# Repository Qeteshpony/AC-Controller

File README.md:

# Qeteshs AC-Controller

[Hardware Documentation](https://qeteshpony.github.io/AC-Controller)

Simple controller for IoT devices with ESP-Home and Home Assistant in mind. This project was mainly started to get better control for our AC system but I guess it can be adapted for about anything. 

The system is based on an ESP32 module, a small LCD and two rotary encoders with optional support for charging and using a LiPo battery. 

The hardware was designed for production by JLCPCB and as many parts as possible were selected from their basic parts library to keep costs low. 

The PCB has two positions for a USB-C port, both are wired in parallel so only one should be soldered in - which one depends on the usecase. 

The display I use is the `DEM 16226 SYH-LY` which is smaller than most 16x2 character displays and available from several retailers. The board most likely needs major changes to be used with another display since the connector is in a different position to most.

I also got shorter 2.54mm headers that only raise the display by about 8mm from the main board so everything is more compact.

The battery used is a 2500 mAH LiPo cell called `LP-785060` with built in protection circuit and about the same measurements as the board so it fits neatly underneath it.

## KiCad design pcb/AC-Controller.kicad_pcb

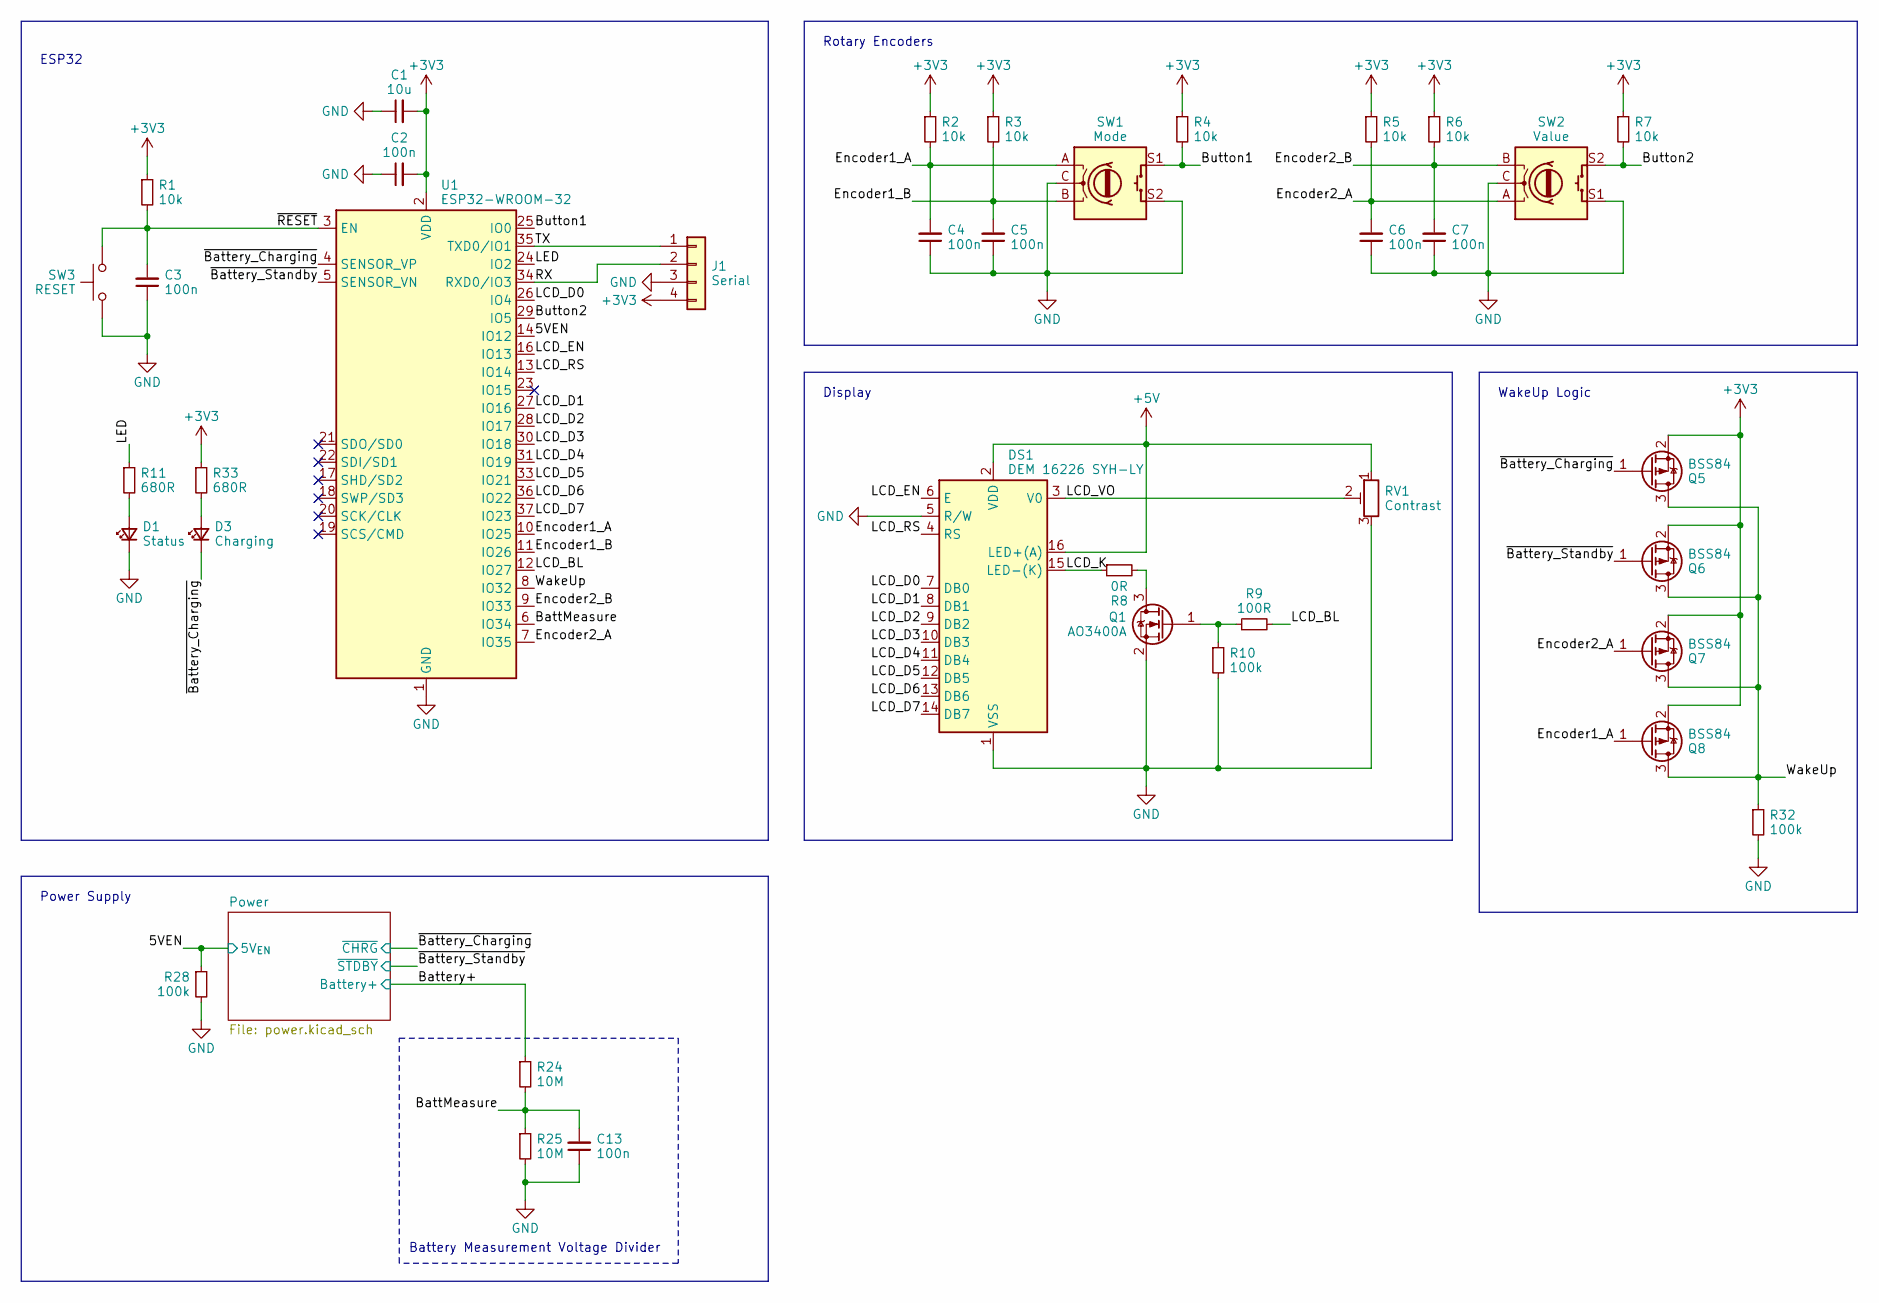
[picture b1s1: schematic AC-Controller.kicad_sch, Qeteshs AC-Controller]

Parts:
C1: 10u; C_0402_1005Metric; LCSC C15525
C2, C3, C4, C5, C6, C7, C13: 100n; C_0402_1005Metric; LCSC C1525
D1: Status; LED_0603_1608Metric; LCSC C2286
D3: Charging; LED_0603_1608Metric; LCSC C2286
DS1: DEM 16226 SYH-LY
J1: Serial; PinSocket_1x04_P2.54mm_Vertical
Q1: AO3400A; SOT-23; LCSC C20917
Q5, Q6, Q7, Q8: BSS84; SOT-23; LCSC C8492
R1, R2, R3, R4, R5, R6, R7: 10k; R_0402_1005Metric; LCSC C25744
R8: 0R; R_0603_1608Metric_Pad0.98x0.95mm_HandSolder; LCSC C21189
R9: 100R; R_0402_1005Metric; LCSC C25076
R10, R28, R32: 100k; R_0402_1005Metric; LCSC C25741
R11, R33: 680R; R_0402_1005Metric; LCSC C25130
R24, R25: 10M; R_0402_1005Metric; LCSC C26082
RV1: Contrast; Potentiometer_Runtron_RM-065_Vertical
SW1: Mode; RotaryEncoder_Alps_EC12E-Switch_Vertical_H20mm
SW2: Value; RotaryEncoder_Alps_EC12E-Switch_Vertical_H20mm
SW3: RESET; SW_Push_1P1T_XKB_TS-1187A; LCSC C318884
U1: ESP32-WROOM-32; LCSC C82899

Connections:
+3V3: C1.2, C2.2, J1.4, Q5.2 (S), Q6.2 (S), Q7.2 (S), Q8.2 (S), R1.1, R2.1, R3.1, R4.1, R5.1, R6.1, R7.1, R33.1, U1.2 (VDD); also elsewhere on the board
+5V: DS1.2 (VDD), DS1.16 (LED+(A)), RV1.1; also elsewhere on the board
/5VEN: R28.1, U1.14 (IO12); also elsewhere on the board
/BattMeasure: C13.2, R24.2, R25.1, U1.6 (IO34)
/Battery+: R24.1; also elsewhere on the board
/Button1: R4.2, SW1.S1, U1.25 (IO0)
/Button2: R7.2, SW2.S2, U1.29 (IO5)
/Encoder1_A: C4.2, Q8.1 (G), R2.2, SW1.A, U1.10 (IO25)
/Encoder1_B: C5.2, R3.2, SW1.B, U1.11 (IO26)
/Encoder2_A: C6.2, Q7.1 (G), R5.2, SW2.A, U1.7 (IO35)
/Encoder2_B: C7.2, R6.2, SW2.B, U1.9 (IO33)
/LCD_BL: R9.2, U1.12 (IO27)
/LCD_D0: DS1.7 (DB0), U1.26 (IO4)
/LCD_D1: DS1.8 (DB1), U1.27 (IO16)
/LCD_D2: DS1.9 (DB2), U1.28 (IO17)
/LCD_D3: DS1.10 (DB3), U1.30 (IO18)
/LCD_D4: DS1.11 (DB4), U1.31 (IO19)
/LCD_D5: DS1.12 (DB5), U1.33 (IO21)
/LCD_D6: DS1.13 (DB6), U1.36 (IO22)
/LCD_D7: DS1.14 (DB7), U1.37 (IO23)
/LCD_EN: DS1.6 (E), U1.16 (IO13)
/LCD_K: DS1.15 (LED-(K)), R8.1
/LCD_RS: DS1.4 (RS), U1.13 (IO14)
/LCD_VO: DS1.3 (V0), RV1.2
/LED: R11.1, U1.24 (IO2)
/RX: J1.2, U1.34 (RXD0/IO3)
/TX: J1.1, U1.35 (TXD0/IO1)
/WakeUp: Q5.3 (D), Q6.3 (D), Q7.3 (D), Q8.3 (D), R32.1, U1.8 (IO32)
/~Battery_Charging: D3.1 (K), Q5.1 (G), U1.4 (SENSOR_VP); also elsewhere on the board
/~Battery_Standby: Q6.1 (G), U1.5 (SENSOR_VN); also elsewhere on the board
/~RESET: C3.2, R1.2, SW3.2, U1.3 (EN)
GND: C1.1, C2.1, C3.1, C4.1, C5.1, C6.1, C7.1, C13.1, D1.1 (K), DS1.1 (VSS), DS1.5 (R/W), J1.3, Q1.2 (S), R10.2, R25.2, R28.2, R32.2, RV1.3, SW1.C, SW1.S2, SW2.C, SW2.S1, SW3.1, U1.1 (GND), U1.15 (GND), U1.38 (GND), U1.39 (GND); also elsewhere on the board
unnamed: D1.2 (A), R11.2
unnamed: D3.2 (A), R33.2
unnamed: Q1.3 (D), R8.2
unnamed: Q1.1 (G), R9.1, R10.1

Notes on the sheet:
Display
WakeUp Logic
ESP32
Battery Measurement Voltage Divider
Power Supply
Rotary Encoders

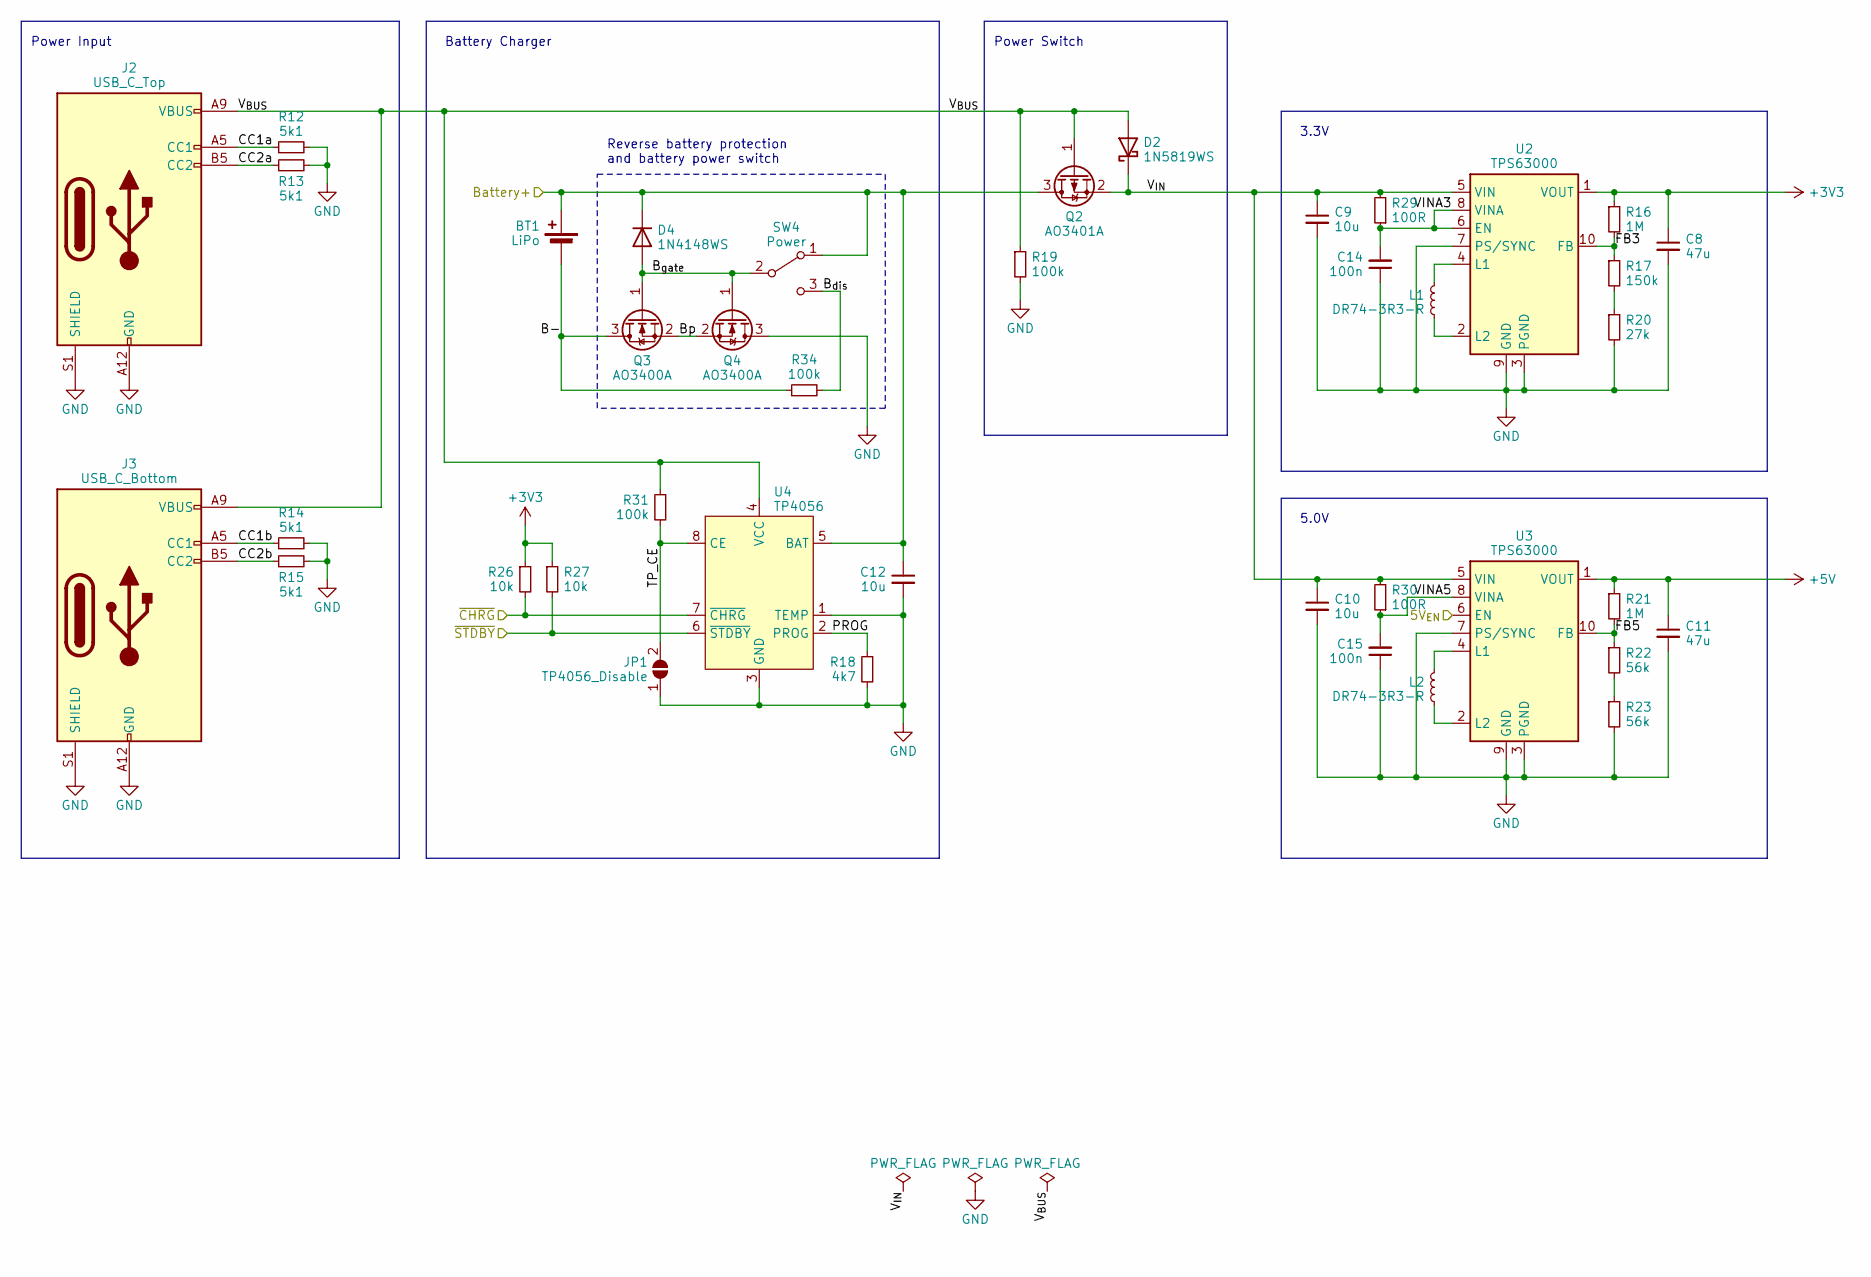
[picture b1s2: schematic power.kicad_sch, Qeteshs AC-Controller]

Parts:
BT1: LiPo; JST_PH_S2B-PH-K_1x02_P2.00mm_Horizontal
C8, C11: 47u; C_0805_2012Metric; LCSC C16780
C9, C10, C12: 10u; C_0603_1608Metric; LCSC C96446
C14, C15: 100n; C_0402_1005Metric; LCSC C1525
D2: 1N5819WS; D_SOD-323; LCSC C191023
D4: 1N4148WS; D_SOD-323; LCSC C2128
J2: USB_C_Top; GCT_USB4125-GF-A_REVA2; LCSC C283540
J3: USB_C_Bottom; GCT_USB4125-GF-A_REVA2; LCSC C283540
JP1: TP4056_Disable; SolderJumper-2_P1.3mm_Open_RoundedPad1.0x1.5mm
L1, L2: DR74-3R3-R; EATON_DR74
Q2: AO3401A; SOT-23; LCSC C15127
Q3, Q4: AO3400A; SOT-23; LCSC C20917
R12, R13, R14, R15: 5k1; R_0402_1005Metric; LCSC C25905
R16, R21: 1M; R_0402_1005Metric; LCSC C26083
R17: 150k; R_0402_1005Metric; LCSC C25755
R18: 4k7; R_0603_1608Metric_Pad0.98x0.95mm_HandSolder; LCSC C23162
R19, R31, R34: 100k; R_0402_1005Metric; LCSC C25741
R20: 27k; R_0402_1005Metric; LCSC C25771
R22, R23: 56k; R_0402_1005Metric; LCSC C25796
R26, R27: 10k; R_0402_1005Metric; LCSC C25744
R29, R30: 100R; R_0402_1005Metric; LCSC C25076
SW4: Power; SW_SPDT_PCM12; LCSC C221841
U2, U3: TPS63000; Texas_DRC0010J; LCSC C24966
U4: TP4056; SOP127P600X175-9N; LCSC C16581

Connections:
+3V3: C8.1, R16.1, R26.1, R27.1, U2.1 (VOUT); also elsewhere on the board
+5V: C11.1, R21.1, U3.1 (VOUT); also elsewhere on the board
/5VEN: U3.6 (EN); also elsewhere on the board
/Battery+: BT1.1 (+), C12.1, D4.1 (K), Q2.3 (D), SW4.1 (A), U4.5 (BAT); also elsewhere on the board
/Power/B-: BT1.2 (-), Q3.3 (D), R34.1
/Power/B_{dis}: R34.2, SW4.3 (C)
/Power/B_{gate}: D4.2 (A), Q3.1 (G), Q4.1 (G), SW4.2 (B)
/Power/Bp: Q3.2 (S), Q4.2 (S)
/Power/CC1a: J2.A5 (CC1), R12.1
/Power/CC1b: J3.A5 (CC1), R14.1
/Power/CC2a: J2.B5 (CC2), R13.1
/Power/CC2b: J3.B5 (CC2), R15.1
/Power/FB3: R16.2, R17.1, U2.10 (FB)
/Power/FB5: R21.2, R22.1, U3.10 (FB)
/Power/PROG: R18.1, U4.2 (PROG)
/Power/TP_CE: JP1.2 (B), R31.2, U4.8 (CE)
/Power/VINA3: C14.2, R29.1, U2.6 (EN), U2.8 (VINA)
/Power/VINA5: C15.2, R30.1, U3.8 (VINA)
/Power/V_{BUS}: D2.2 (A), J2.A9 (VBUS), J2.B9 (VBUS), J3.A9 (VBUS), J3.B9 (VBUS), Q2.1 (G), R19.1, R31.1, U4.4 (VCC)
/Power/V_{IN}: C9.1, C10.1, D2.1 (K), Q2.2 (S), R29.2, R30.2, U2.5 (VIN), U3.5 (VIN)
/~Battery_Charging: R26.2, U4.7 (~CHRG); also elsewhere on the board
/~Battery_Standby: R27.2, U4.6 (~STDBY); also elsewhere on the board
GND: C8.2, C9.2, C10.2, C11.2, C12.2, C14.1, C15.1, J2.A12 (GND), J2.B12 (GND), J2.S1 (SHIELD), J3.A12 (GND), J3.B12 (GND), J3.S1 (SHIELD), JP1.1 (A), Q4.3 (D), R12.2, R13.2, R14.2, R15.2, R18.2, R19.2, R20.2, R23.2, U2.3 (PGND), U2.7 (PS/SYNC), U2.9 (GND), U2.11 (PGND), U3.3 (PGND), U3.7 (PS/SYNC), U3.9 (GND), U3.11 (PGND), U4.1 (TEMP), U4.3 (GND), U4.9 (EP); also elsewhere on the board
unnamed: R17.2, R20.1
unnamed: R22.2, R23.1
unnamed: L1.2, U2.4 (L1)
unnamed: L1.1, U2.2 (L2)
unnamed: L2.2, U3.4 (L1)
unnamed: L2.1, U3.2 (L2)

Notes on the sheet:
Power Input
Power Switch
3.3V
Battery Charger
5.0V
Reverse battery protection and battery power switch

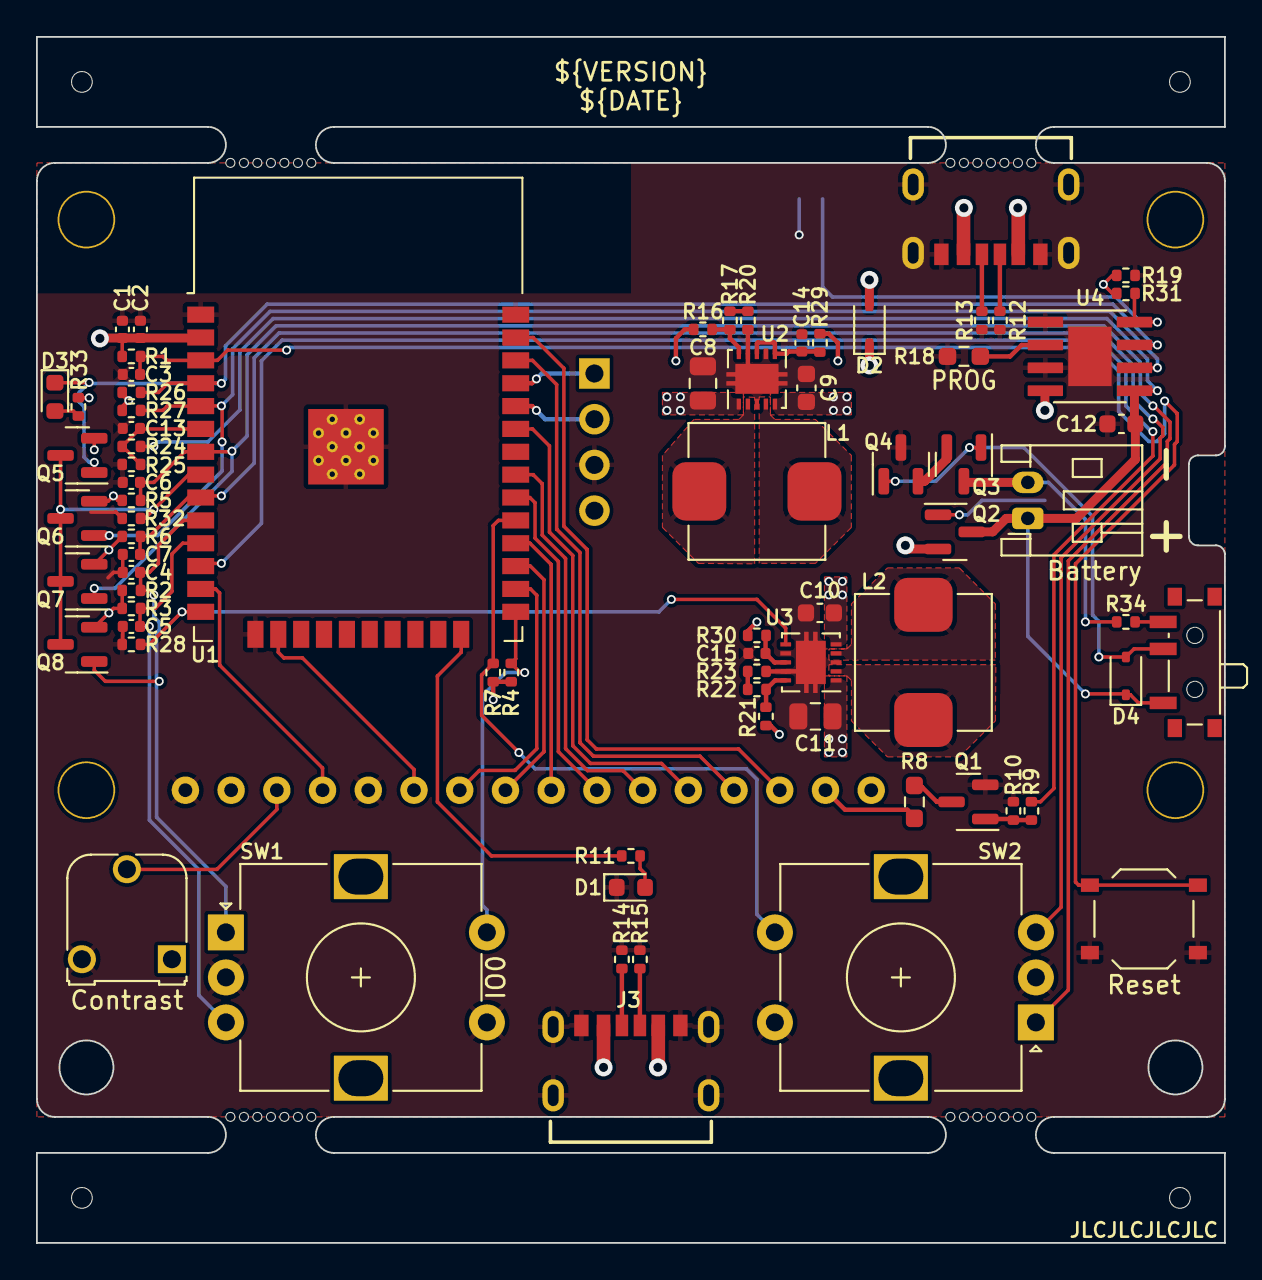
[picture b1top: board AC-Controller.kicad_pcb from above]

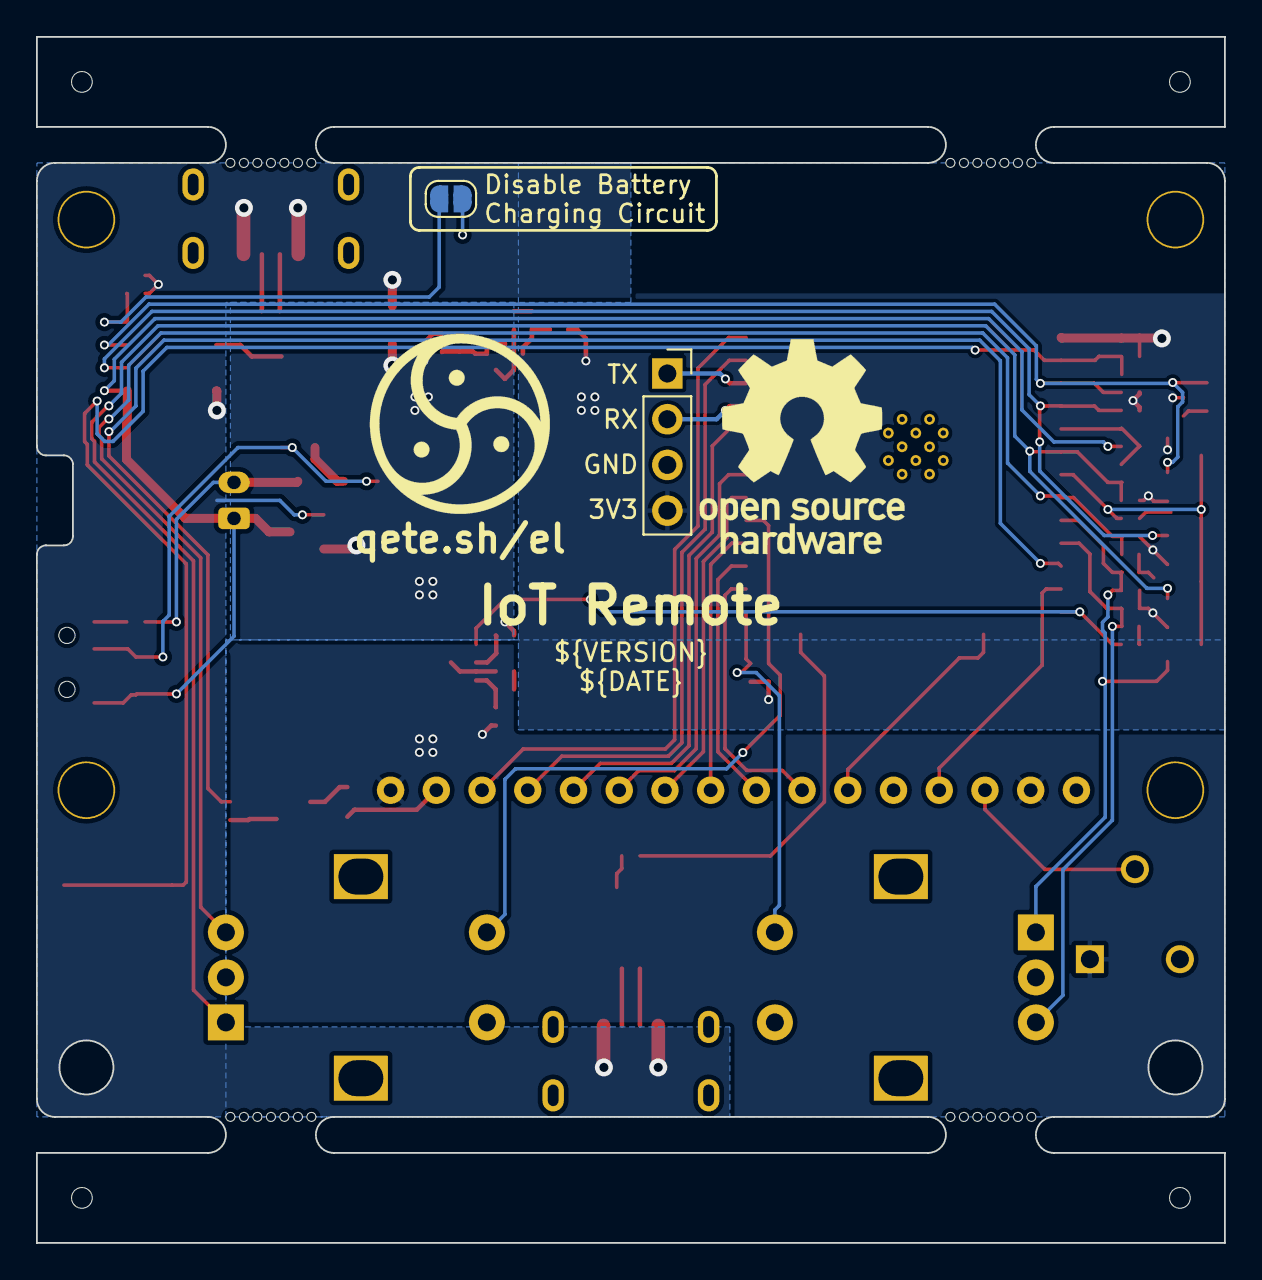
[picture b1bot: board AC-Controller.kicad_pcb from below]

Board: 2 copper layers, 66.0 x 67.0 mm, 82 parts (2 on the bottom side), 58 nets.

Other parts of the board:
mouse-bite-2mm-slot, mouse-bite-2mm-slot#2, mouse-bite-2mm-slot#3, mouse-bite-2mm-slot#4: VAL**; mouse-bite-2x5mm-slot-onesided-v2

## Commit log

2023-06-29 feat: initial commit
2023-06-30 docs: add CI badge
2023-06-30 style: schematics cleanup
2023-06-30 ci: disable checks
    Disable ERC and DRC for now since they throw errors during CI that i still need to solve. The checks are done locally before committing though.
2023-06-30 ci: fix 3d render rotation
2023-06-30 style: use correct variables
2023-06-30 docs: add render and hardware docs
2023-06-30 style: add 3d models for pcb render
2023-07-16 feat: add battery protection
2023-07-17 feat: add reverse polarity protection for battery input
    just to make sure a reverse connected battery won't kill the circuit
2023-07-21 fix: add missing JLC part numbers
2023-07-21 chore(main): release 1.0.0
2023-08-03 feat: add Reset button
2023-08-03 fix: turn around battery connector
    Battery connector was not reachable with display installed
2023-08-05 feat: remove battery protection IC
    Since I only use protected battery packs (which is highly recommended) the additional protection IC on the PCB was obsolete and only raised production cost.
2023-08-05 feat: add charging indicator LED
2023-08-05 feat: replace contrast pot with more common type
2023-08-05 feat: replace TP4056 Prog Resistor footprint with 0603
    Replace the footprint for the programming resistor to 0603 to make replacing it easier. Also changing the default value to 4.7k for slower charge and less heat production
2023-08-05 feat: add cutout for battery cable
2023-08-06 feat: add disable jumper for battery charger
    Adding a jumper to disable the TP4056 Battery Charger IC in case no battery is connected and the device is powered by USB only. No need for the IC to draw power in that case.
2023-08-06 docs: add info about display and battery
2023-08-06 style: board and schematics cleanup
2023-08-06 docs: wording
2023-08-07 feat: add more ways to wake up
    Adding simple MOSFET logic to watch 4 signals for waking up from deep sleep
2023-08-08 feat: add power switch
    Add switch to disconnect battery power from the circuit for when the device is not in use for a long time and reduce power consumption to a few nA
2023-08-10 style: cleanup
2023-08-12 fix: add missing part numbers
2023-08-12 chore(main): release 1.1.0
2023-08-12 docs: fix typo
2024-08-29 ci: remove dependency between jobs
